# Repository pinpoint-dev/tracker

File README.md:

# tracker
The PinPoint tracker module pcb and cad files

This repository contains all the KiCAD EDA files and Fusion 360 CAD designs for the PinPoint tracker modules

### Features
- nRF52832-based board - [Ebyte E73-2G4M08S1E](https://www.cdebyte.com/products/E73-2G4M08S1E/2)
- Compatible with Apple's FindMy network through [OpenHaystack](https://github.com/seemoo-lab/openhaystack)
- Small form factor (ideally less than 30x30x10mm)
- Location Pin shape
- RGB led for flair
- piezo buzzer for finding

### Repository structure
- `pcb/` contains the KiCAD EDA files for the tracker module
- `cad/` contains the Fusion 360 CAD files for the tracker module
- `docs/` contains the datasheets and other documentation for the components used in the tracker module
- `LICENSE` contains the license information for the repository
- `README.md` contains the information about the repository

### Board To-Do
- [x] battery holder
- [x] mounting holes
- [x] SWD connector
- [x] piezo buzzer
- [x] USB interface
- [x] RGB led

### License

This project is licensed under the TAPR Open Hardware License. See [LICENSE.txt](/LICENSE.txt) for more information.

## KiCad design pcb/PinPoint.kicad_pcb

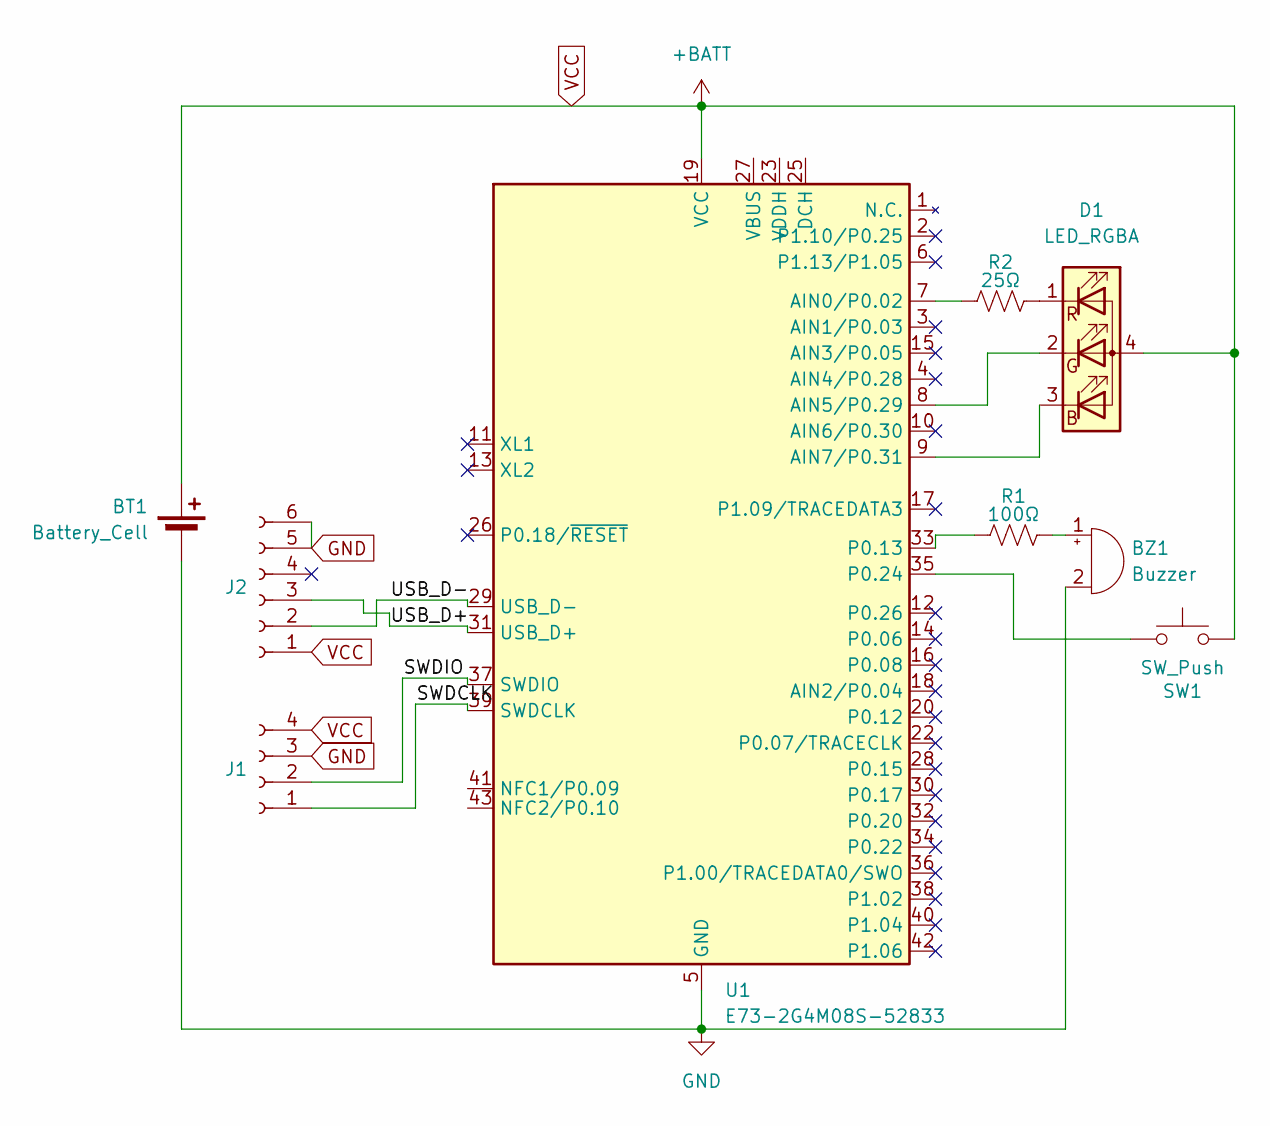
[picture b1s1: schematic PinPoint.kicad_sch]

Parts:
BT1: Battery_Cell; BatteryHolder_Keystone_3034_1x20mm; LCSC Part # C964823
BZ1: Buzzer; Buzzer_Murata_PKMCS0909E; LCSC Part # C910763
D1: LED_RGBA; LED_LiteOn_LTST-C19HE1WT; LCSC Part # C458749
J1: PinHeader_1x04_P2.54mm_Vertical
J2: USB_Micro-B_Molex_47346-0001; LCSC Part # C132560
R1: 100Ω; R_0603_1608Metric
R2: 25Ω; R_0603_1608Metric
SW1: SW_Push; SW_SPST_CK_KXT3; LCSC Part # C388289
U1: E73-2G4M08S-52833; E73-2G4M08S1E; LCSC Part # C356849

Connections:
/SWDCLK: J1.1, U1.39 (SWDCLK)
/SWDIO: J1.2, U1.37 (SWDIO)
/USB_D+: J2.3, U1.31 (USB_D+)
/USB_D-: J2.2, U1.29 (USB_D-)
GND: BT1.2 (-), BZ1.2 (-), J1.3, J2.5, J2.6, U1.5 (GND), U1.21 (GND), U1.24 (GND)
unnamed: BZ1.1 (+), R1.2
unnamed: D1.3 (BK), U1.9 (AIN7/P0.31)
unnamed: D1.2 (GK), U1.8 (AIN5/P0.29)
unnamed: D1.1 (RK), R2.2
unnamed: R2.1, U1.7 (AIN0/P0.02)
unnamed: R1.1, U1.33 (P0.13)
unnamed: SW1.1, U1.35 (P0.24)
VCC: BT1.1 (+), D1.4 (A), J1.4, J2.1, SW1.2, U1.19 (VCC)

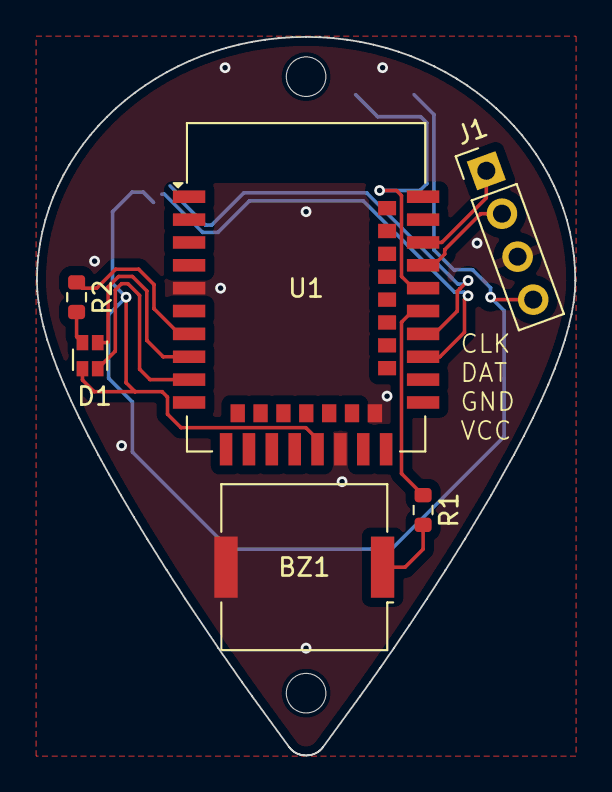
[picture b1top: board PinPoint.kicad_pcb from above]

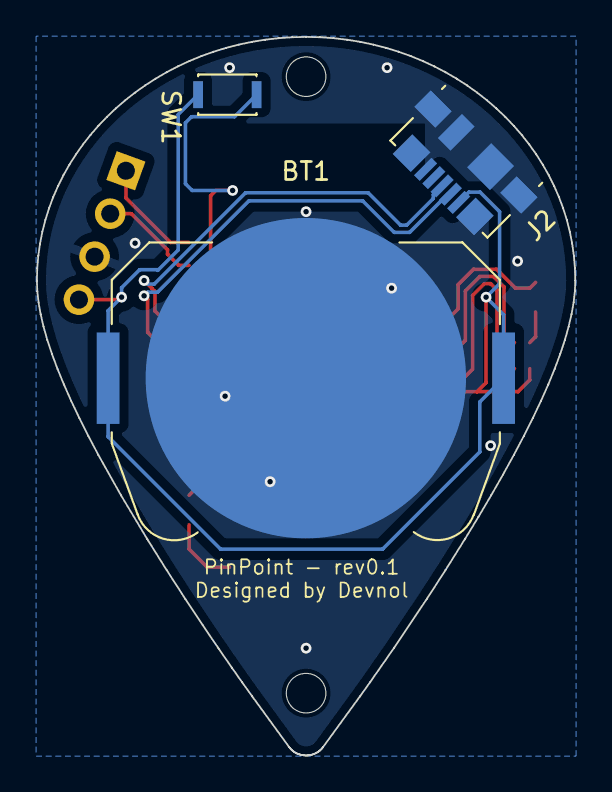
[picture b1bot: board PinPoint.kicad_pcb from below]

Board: 2 copper layers, 29.9 x 39.9 mm, 9 parts (3 on the bottom side), 13 nets.

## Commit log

2024-07-04 Add LICENSE, populate README with basic information
2024-07-04 Add some initial design notes for the device layout
2024-07-05 Added datasheets for IC and carrier board
2024-07-05 Create local project libraries and import footprint and 3d model
2024-07-05 Import footprint for board from builtin kicad symbol E73-2G4M04S-52832
2024-07-05 Update pin table on RF Module Symbol Replace nRF52 datasheet with latest version
2024-07-05 Organize RF Module pinout in KiCad Sym
2024-07-05 Begin schematic from routing ground, fix error in Sym
2024-07-06 Fix Module footprint, replace 3d model
2024-07-07 Create board outline, change battery holder
2024-07-07 Add screw holes, debug port
2024-07-07 Add buzzer, include todo list for board features
2024-07-08 Jankily add microUSB port
2024-07-08 Complete board, add fab outputs
2024-07-09 Add push button
2024-07-09 Replace buzzer for active Add missing 3d models from lcsc
